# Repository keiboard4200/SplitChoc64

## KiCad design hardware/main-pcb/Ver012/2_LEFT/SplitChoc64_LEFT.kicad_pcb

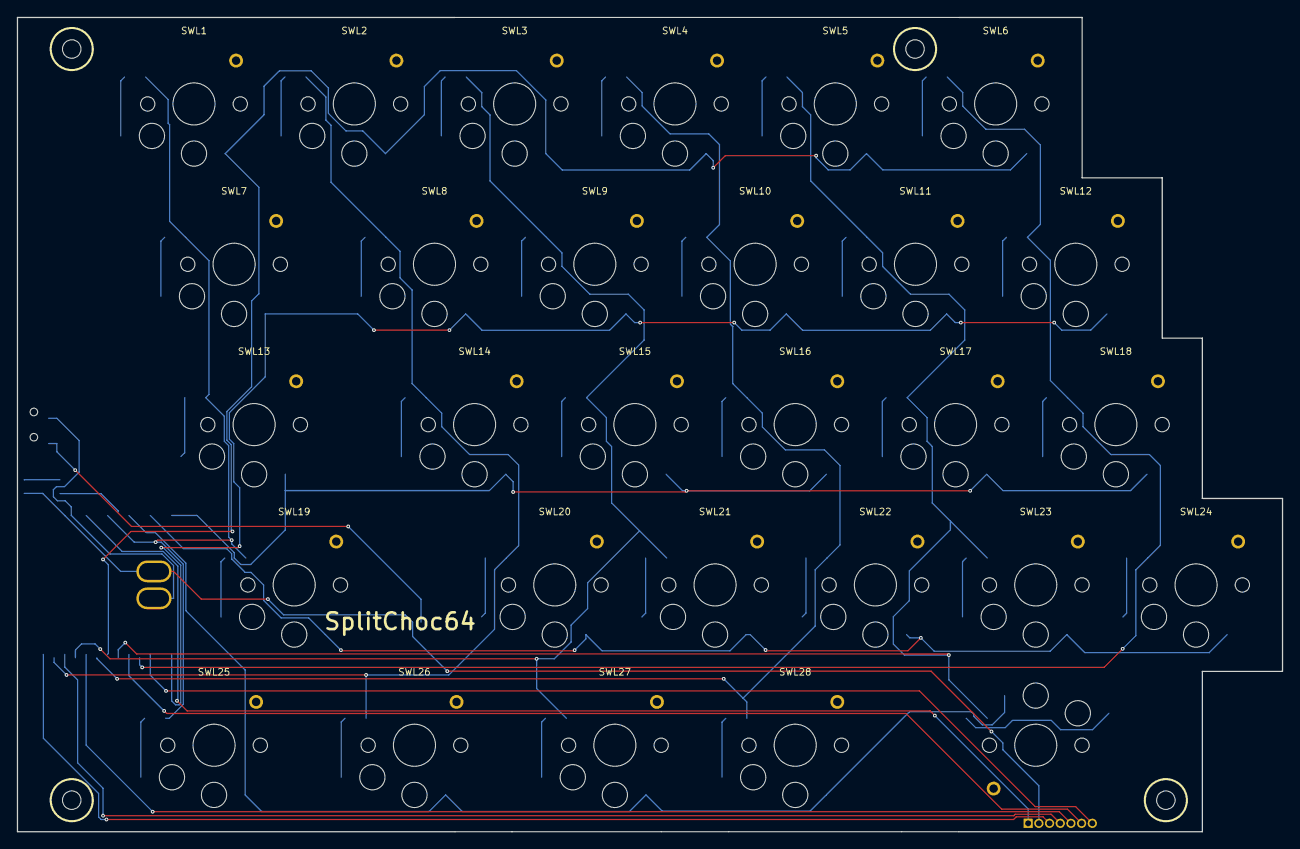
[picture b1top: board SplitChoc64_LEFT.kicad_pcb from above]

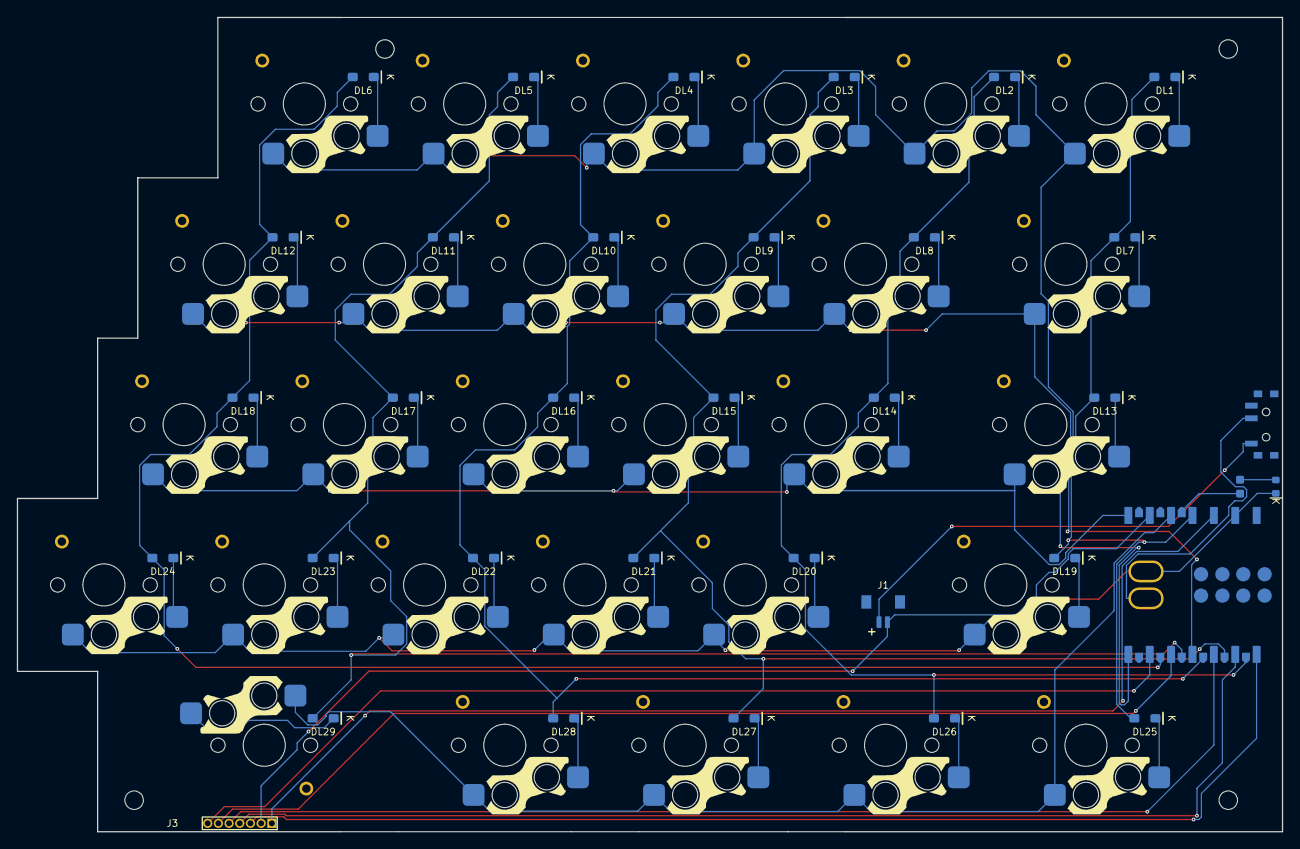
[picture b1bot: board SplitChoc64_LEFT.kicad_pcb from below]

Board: 2 copper layers, 150.3 x 96.8 mm, 68 parts (35 on the bottom side), 51 nets.

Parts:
DL1: 1N4148WS; DL1
DL2: 1N4148WS; DL2
DL3: 1N4148WS; DL3
DL4: 1N4148WS; DL4
DL5: 1N4148WS; DL5
DL6: 1N4148WS; DL6
DL7: 1N4148WS; DL7
DL8: 1N4148WS; DL8
DL9: 1N4148WS; DL9
DL10: 1N4148WS; DL10
DL11: 1N4148WS; DL11
DL12: 1N4148WS; DL12
DL13: 1N4148WS; DL13
DL14: 1N4148WS; DL14
DL15: 1N4148WS; DL15
DL16: 1N4148WS; DL16
DL17: 1N4148WS; DL17
DL18: 1N4148WS; DL18
DL19: 1N4148WS; DL19
DL20: 1N4148WS; DL20
DL21: 1N4148WS; DL21
DL22: 1N4148WS; DL22
DL23: 1N4148WS; DL23
DL24: 1N4148WS; DL24
DL25: 1N4148WS; DL25
DL26: 1N4148WS; DL26
DL27: 1N4148WS; DL27
DL28: 1N4148WS; DL28
DL29: 1N4148WS; DL29
DLED1: KT-0603B; LED_0603_TOP_BLUE
H1, H2, H3, H4: M2_CASE_MOUNT
J1: BM02B-SRSS-TB; J1
J3: 3V3 GND X Y SW SDA SCL; J3
RLED1: 100R; STATUS_R_0603
SWL1: Kailh Choc V2 / HotSwap; SWL1
SWL2: Kailh Choc V2 / HotSwap; SWL2
SWL3: Kailh Choc V2 / HotSwap; SWL3
SWL4: Kailh Choc V2 / HotSwap; SWL4
SWL5: Kailh Choc V2 / HotSwap; SWL5
SWL6: Kailh Choc V2 / HotSwap; SWL6
SWL7: Kailh Choc V2 / HotSwap; SWL7
SWL8: Kailh Choc V2 / HotSwap; SWL8
SWL9: Kailh Choc V2 / HotSwap; SWL9
SWL10: Kailh Choc V2 / HotSwap; SWL10
SWL11: Kailh Choc V2 / HotSwap; SWL11
SWL12: Kailh Choc V2 / HotSwap; SWL12
SWL13: Kailh Choc V2 / HotSwap; SWL13
SWL14: Kailh Choc V2 / HotSwap; SWL14
SWL15: Kailh Choc V2 / HotSwap; SWL15
SWL16: Kailh Choc V2 / HotSwap; SWL16
SWL17: Kailh Choc V2 / HotSwap; SWL17
SWL18: Kailh Choc V2 / HotSwap; SWL18
SWL19: Kailh Choc V2 / HotSwap; SWL19
SWL20: Kailh Choc V2 / HotSwap; SWL20
SWL21: Kailh Choc V2 / HotSwap; SWL21
SWL22: Kailh Choc V2 / HotSwap; SWL22
SWL23: Kailh Choc V2 / HotSwap; SWL23
SWL24: Kailh Choc V2 / HotSwap; SWL24
SWL25: Kailh Choc V2 / HotSwap; SWL25
SWL26: Kailh Choc V2 / HotSwap; SWL26
SWL27: Kailh Choc V2 / HotSwap; SWL27
SWL28: Kailh Choc V2 / HotSwap; SWL28
SWL29: Kailh Choc V2 / HotSwap; SWL29
SWP1: PCM12SMTR; SWP1
U1: XIAO nRF52840 Plus; U1

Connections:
L_3V3: J3.1, U1.12
L_BAT_RAW: J1.1, SWP1.1
L_BAT_SW: SWP1.2, U1.32
L_COL0: DL1.2, DL7.2, DL13.2, DL19.2, DL25.2, U1.11
L_COL1: DL2.2, DL8.2, DL14.2, DL20.2, DL26.2, U1.15
L_COL2: DL3.2, DL9.2, DL15.2, DL21.2, DL27.2, U1.16
L_COL3: DL4.2, DL10.2, DL16.2, DL22.2, DL28.2, U1.17
L_COL4: DL5.2, DL11.2, DL17.2, DL23.2, DL29.2, U1.18
L_COL5: DL6.2, DL12.2, DL18.2, DL24.2, U1.19
L_GND: DLED1.1, J1.2, J3.2, U1.13, U1.33
L_JOY_SCL: J3.7, U1.6
L_JOY_SDA: J3.6, U1.5
L_JOY_SW: J3.5, U1.3
L_JOY_X: J3.3, U1.1
L_JOY_Y: J3.4, U1.2
L_K1_D: DL1.1, SWL1.2
L_K2_D: DL2.1, SWL2.2
L_K3_D: DL3.1, SWL3.2
L_K4_D: DL4.1, SWL4.2
L_K5_D: DL5.1, SWL5.2
L_K6_D: DL6.1, SWL6.2
L_K7_D: DL7.1, SWL7.2
L_K8_D: DL8.1, SWL8.2
L_K9_D: DL9.1, SWL9.2
L_K10_D: DL10.1, SWL10.2
L_K11_D: DL11.1, SWL11.2
L_K12_D: DL12.1, SWL12.2
L_K13_D: DL13.1, SWL13.2
L_K14_D: DL14.1, SWL14.2
L_K15_D: DL15.1, SWL15.2
L_K16_D: DL16.1, SWL16.2
L_K17_D: DL17.1, SWL17.2
L_K18_D: DL18.1, SWL18.2
L_K19_D: DL19.1, SWL19.2
L_K20_D: DL20.1, SWL20.2
L_K21_D: DL21.1, SWL21.2
L_K22_D: DL22.1, SWL22.2
L_K23_D: DL23.1, SWL23.2
L_K24_D: DL24.1, SWL24.2
L_K25_D: DL25.1, SWL25.2
L_K26_D: DL26.1, SWL26.2
L_K27_D: DL27.1, SWL27.2
L_K28_D: DL28.1, SWL28.2
L_K29_D: DL29.1, SWL29.2
L_LED_A: DLED1.2, RLED1.2
L_LED_CTRL: RLED1.1, U1.23
L_ROW0: SWL1.1, SWL2.1, SWL3.1, SWL4.1, SWL5.1, SWL6.1, U1.4
L_ROW1: SWL7.1, SWL8.1, SWL9.1, SWL10.1, SWL11.1, SWL12.1, U1.7
L_ROW2: SWL13.1, SWL14.1, SWL15.1, SWL16.1, SWL17.1, SWL18.1, U1.8
L_ROW3: SWL19.1, SWL20.1, SWL21.1, SWL22.1, SWL23.1, SWL24.1, U1.9
L_ROW4: SWL25.1, SWL26.1, SWL27.1, SWL28.1, SWL29.1, U1.10
